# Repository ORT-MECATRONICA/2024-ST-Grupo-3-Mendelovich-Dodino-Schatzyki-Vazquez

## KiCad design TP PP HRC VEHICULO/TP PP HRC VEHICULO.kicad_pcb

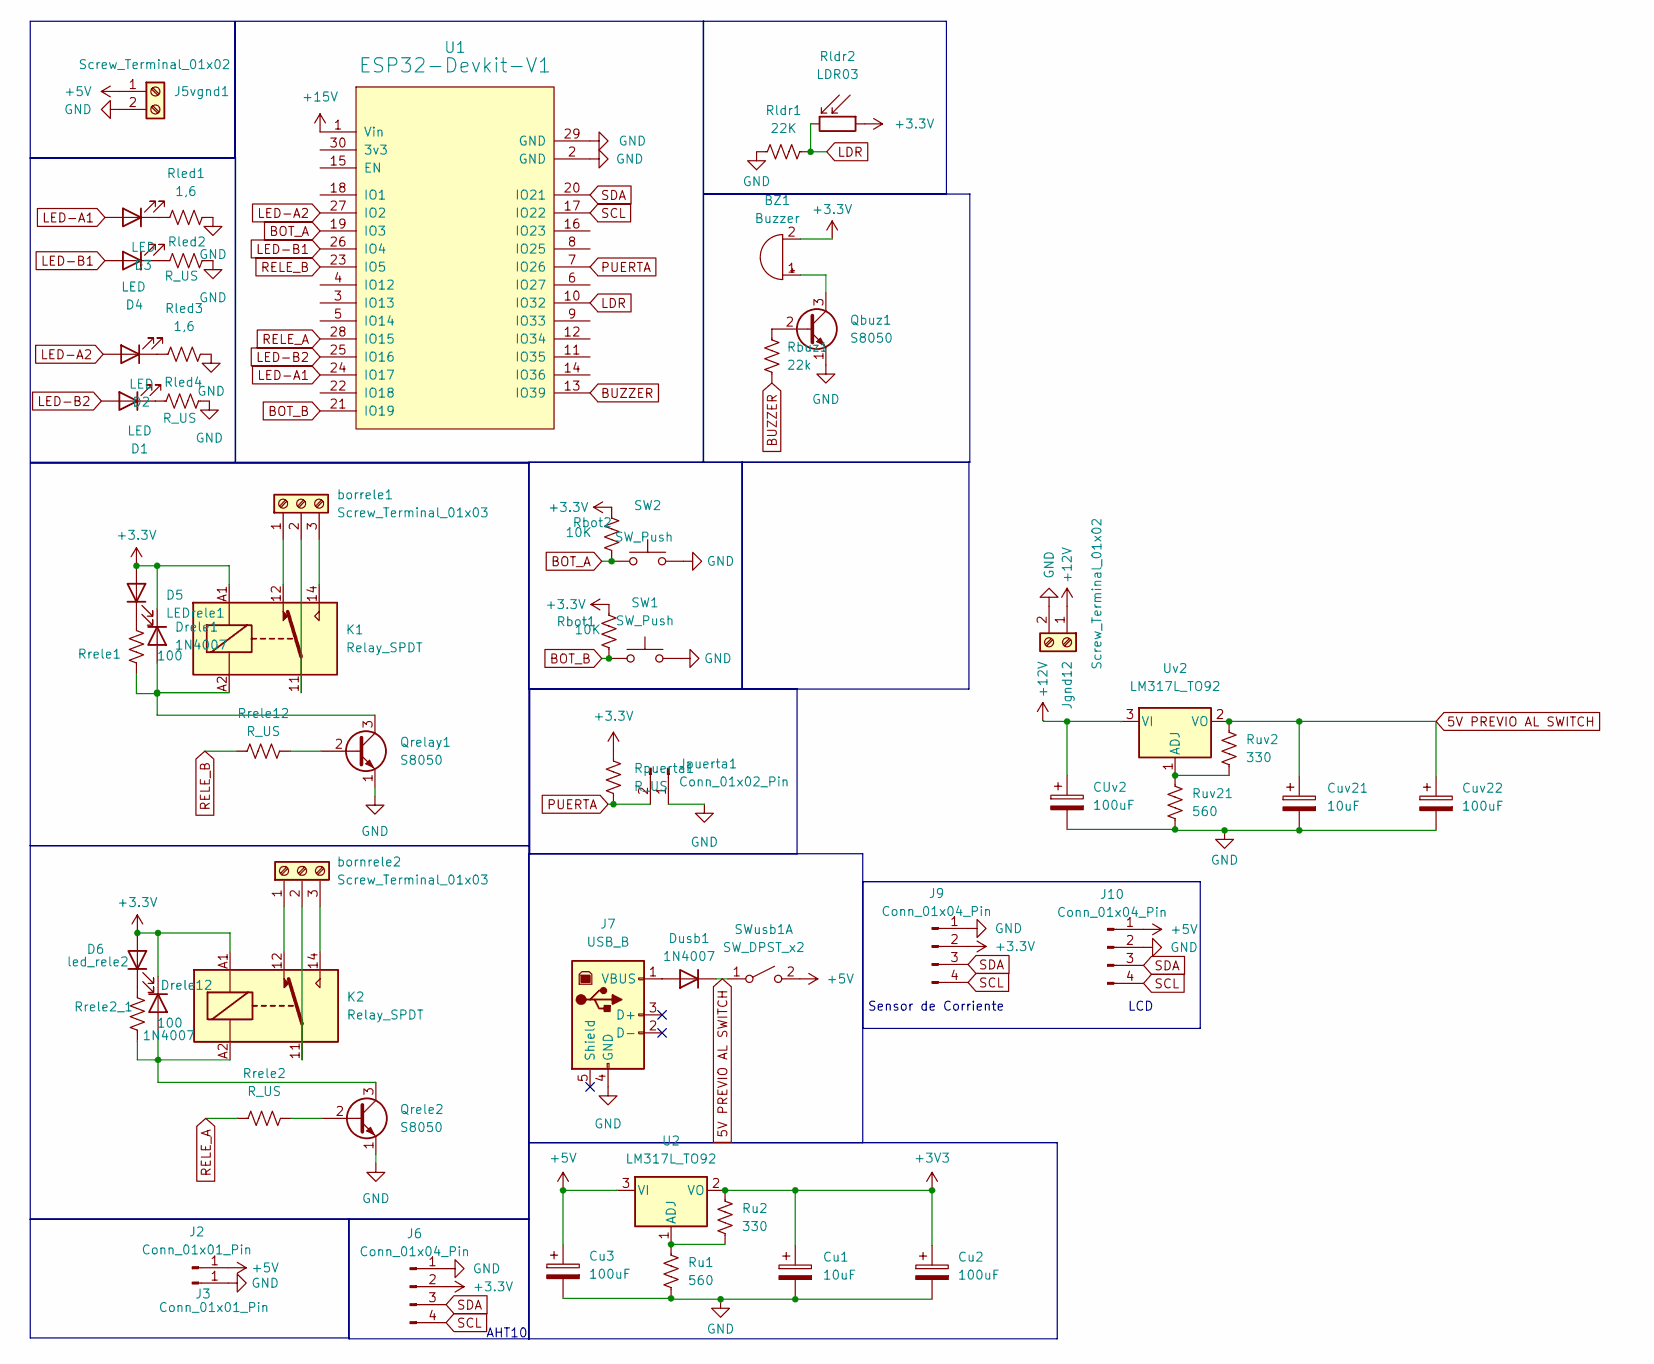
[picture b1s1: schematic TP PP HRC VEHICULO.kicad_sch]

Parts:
BZ1: Buzzer; Buzzer_12x9.5RM7.6
CUv2: 100uF; CP_Radial_D10.0mm_P3.50mm
Cu1: 10uF; CP_Radial_D5.0mm_P2.50mm
Cu2: 100uF; C_Disc_D7.5mm_W4.4mm_P5.00mm
Cu3: 100uF; CP_Radial_D10.0mm_P3.50mm
Cuv21: 10uF; CP_Radial_D5.0mm_P2.50mm
Cuv22: 100uF; C_Disc_D7.5mm_W4.4mm_P5.00mm
D1, D2, D3, D4: LED; Molex_KK-254_AE-6410-02A_1x02_P2.54mm_Vertical
D5: LEDrele1; LED_D5.0mm
D6: led_rele2; LED_D5.0mm
Drele1, Drele12: 1N4007; D_DO-41_SOD81_P10.16mm_Horizontal
Dusb1: 1N4007; D_DO-41_SOD81_P10.16mm_Horizontal
J2, J3: Conn_01x01_Pin; PinHeader_1x01_P2.54mm_Vertical
J5vgnd1: Screw_Terminal_01x02; TerminalBlock_bornier-2_P5.08mm
J6, J9, J10: Conn_01x04_Pin; Molex_KK-254_AE-6410-04A_1x04_P2.54mm_Vertical
J7: USB_B; USB_B_OST_USB-B1HSxx_Horizontal
Jgnd12: Screw_Terminal_01x02; TerminalBlock_bornier-2_P5.08mm
Jpuerta1: Conn_01x02_Pin; Molex_KK-254_AE-6410-02A_1x02_P2.54mm_Vertical
K1, K2: Relay_SPDT; Relay_SPDT_Finder_36.11
Qbuz1: S8050; TO-92_Inline
Qrelay1: S8050; TO-92_Inline
Qrele2: S8050; TO-92_Inline
Rbot1, Rbot2: 10K; R_Axial_DIN0207_L6.3mm_D2.5mm_P10.16mm_Horizontal
Rbuz1: 22k; R_Axial_DIN0207_L6.3mm_D2.5mm_P10.16mm_Horizontal
Rldr1: 22K; R_Axial_DIN0207_L6.3mm_D2.5mm_P10.16mm_Horizontal
Rldr2: LDR03; Molex_KK-254_AE-6410-02A_1x02_P2.54mm_Vertical
Rled1, Rled3: 1,6; R_Axial_DIN0207_L6.3mm_D2.5mm_P10.16mm_Horizontal
Rled2, Rled4: R_US; R_Axial_DIN0207_L6.3mm_D2.5mm_P10.16mm_Horizontal
Rpuerta1: R_US; R_Axial_DIN0207_L6.3mm_D2.5mm_P10.16mm_Horizontal
Rrele1, Rrele2_1: 100; R_Axial_DIN0207_L6.3mm_D2.5mm_P10.16mm_Horizontal
Rrele2, Rrele12: R_US; R_Axial_DIN0207_L6.3mm_D2.5mm_P10.16mm_Horizontal
Ru1: 560; R_Axial_DIN0207_L6.3mm_D2.5mm_P10.16mm_Horizontal
Ru2: 330; R_Axial_DIN0207_L6.3mm_D2.5mm_P10.16mm_Horizontal
Ruv2: 330; R_Axial_DIN0207_L6.3mm_D2.5mm_P10.16mm_Horizontal
Ruv21: 560; R_Axial_DIN0207_L6.3mm_D2.5mm_P10.16mm_Horizontal
SW1, SW2: SW_Push; Molex_KK-254_AE-6410-02A_1x02_P2.54mm_Vertical
SWusb1: SW_DPST_x2; TerminalBlock_bornier-2_P5.08mm
U1: ESP32-Devkit-V1; DOIT_ESP32_Devkit_mirko
U2: LM317L_TO92; TO-92_Inline
Uv2: LM317L_TO92; TO-92_Inline
bornrele2: Screw_Terminal_01x03; TerminalBlock_bornier-3_P5.08mm
borrele1: Screw_Terminal_01x03; TerminalBlock_bornier-3_P5.08mm

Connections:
5V PREVIO AL SWITCH: Cuv21.1, Cuv22.1, Dusb1.1 (K), Ruv2.1, SWusb1.1 (A), Uv2.2 (VO)
+3.3V: BZ1.2 (+), D5.2 (A), D6.2 (A), Drele1.1 (K), Drele12.1 (K), J6.2, J9.2, K1.A1, K2.A1, Rbot1.2, Rbot2.2, Rldr2.1, Rpuerta1.1
+3V3: Cu1.1, Cu2.1, Ru2.1, U2.2 (VO)
+5V: Cu3.1, J2.1, J5vgnd1.1, J10.1, SWusb1.2 (B), U2.3 (VI)
+12V: CUv2.1, Jgnd12.1, Uv2.3 (VI)
+15V: U1.1 (Vin)
BOT_A: Rbot2.1, SW2.1, U1.19 (IO3), U1.22 (IO18)
BOT_B: Rbot1.1, SW1.1, U1.21 (IO19)
BUZZER: Rbuz1.2, U1.13 (IO39)
GND: CUv2.2, Cu1.2, Cu2.2, Cu3.2, Cuv21.2, Cuv22.2, J3.1, J5vgnd1.2, J6.1, J7.4 (GND), J9.1, J10.2, Jgnd12.2, Jpuerta1.1, Qbuz1.1 (E), Qrelay1.1 (E), Qrele2.1 (E), Rldr1.1, Rled1.2, Rled2.2, Rled3.2, Rled4.2, Ru1.2, Ruv21.2, SW1.2, SW2.2, U1.2 (GND), U1.29 (GND)
LDR: Rldr1.2, Rldr2.2, U1.10 (IO32)
LED-A1: D3.2 (A), U1.24 (IO17)
LED-A2: D2.2 (A), U1.27 (IO2)
LED-B1: D4.2 (A), U1.26 (IO4)
LED-B2: D1.2 (A), U1.25 (IO16)
unnamed: BZ1.1 (-), Qbuz1.3 (C)
unnamed: D1.1 (K), Rled4.1
unnamed: D2.1 (K), Rled3.1
unnamed: D3.1 (K), Rled1.1
unnamed: D4.1 (K), Rled2.1
unnamed: D5.1 (K), Rrele1.2
unnamed: D6.1 (K), Rrele2_1.2
unnamed: Drele1.2 (A), K1.A2, Qrelay1.3 (C), Rrele1.1
unnamed: Drele12.2 (A), K2.A2, Qrele2.3 (C), Rrele2_1.1
unnamed: Dusb1.2 (A), J7.1 (VBUS)
unnamed: Qbuz1.2 (B), Rbuz1.1
unnamed: Qrelay1.2 (B), Rrele12.2
unnamed: Qrele2.2 (B), Rrele2.2
unnamed: Ru1.1, Ru2.2, U2.1 (ADJ)
unnamed: Ruv2.2, Ruv21.1, Uv2.1 (ADJ)
unnamed: K2.12, bornrele2.1
unnamed: K2.11, bornrele2.2
unnamed: K2.14, bornrele2.3
unnamed: K1.12, borrele1.1
unnamed: K1.11, borrele1.2
unnamed: K1.14, borrele1.3
PUERTA: Jpuerta1.2, Rpuerta1.2, U1.7 (IO26)
RELE_A: Rrele2.1, U1.28 (IO15)
RELE_B: Rrele12.1, U1.23 (IO5)
SCL: J6.4, J9.4, J10.4, U1.17 (IO22)
SDA: J6.3, J9.3, J10.3, U1.20 (IO21)

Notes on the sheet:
Sensor de Corriente
LCD
AHT10

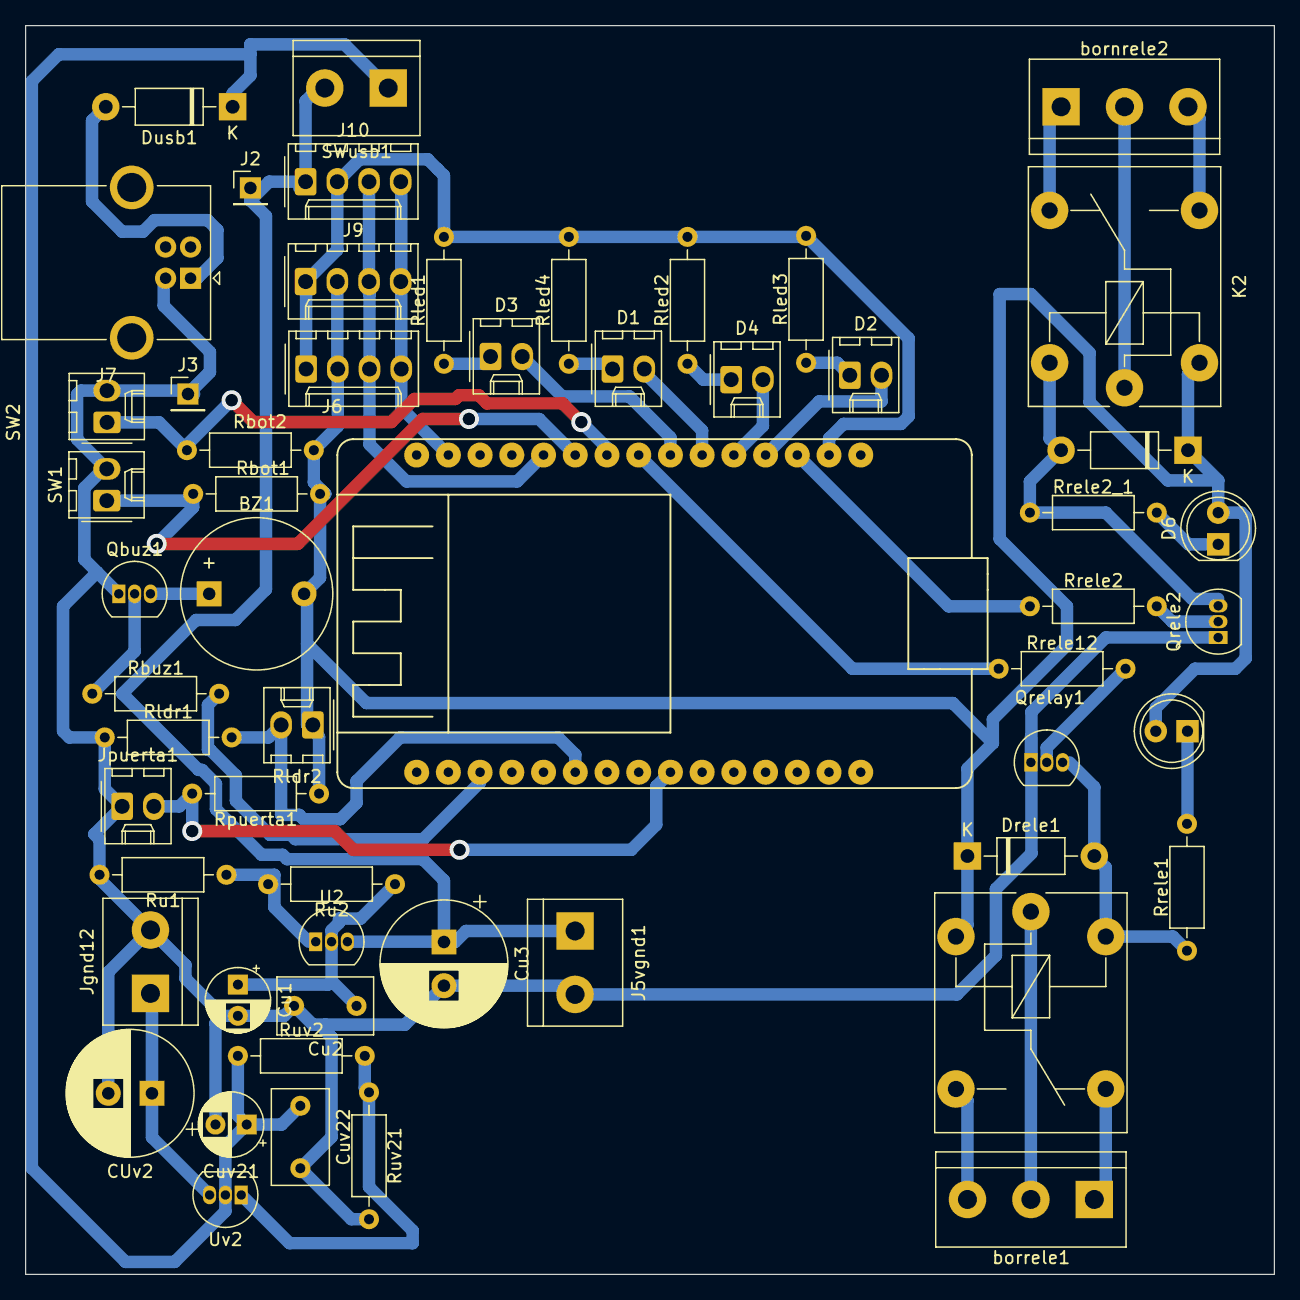
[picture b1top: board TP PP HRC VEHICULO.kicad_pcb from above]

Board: 2 copper layers, 100.0 x 100.0 mm, 56 parts (0 on the bottom side), 40 nets.

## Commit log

2024-05-21 ST-TP3
2024-06-11 maquina de estado
2024-07-06 Foto Maquina de estado - Entregado por Rafael Vazquez y Ezequiel Dodino
2024-09-24 AUTO
2024-10-01 placa
2024-10-01 placa actualizada
2024-10-10 terminado
2024-10-10 suuuuuu
